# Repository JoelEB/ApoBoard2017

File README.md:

2017 Propagand-Eye
=======================================

This is the development repo for the 2017 Apogaea soldering Workshop project, the Propagand-Eye. 

For all final files for tutorials on how to hack your eyeball, please visit [https://github.com/apoboard](https://github.com/apoboard). 

To donate to this project, please send donations to joeleb on Venmo. 

This board uses an Atmega328p microcontroller (the same device in the Arduino Uno) and can be programmed with an FTDI serial adapter and the Arduino IDE. There is a DC/DC boost-converter (the PAM2401) to provide 5 volts from a single AA battery. On board are 10 addressable WS2812 LEDs (the same LEDs used on all Neopixel products). There is also an infrared (IR) transmitter/receiver pair that allows the boards to communicate with one another. A tactile button is also provided to switch through modes.

License Information
-------------------

All of these files are developed for free, for Apogaea, and for fun. It is publicly available under the GNU General Public License version 2 (the "GPL License"). For more information, please see: http://www.gnu.org/licenses/gpl-2.0.html

Copyright (c) John English, Joel Bartlett, 2017 Licensing: GPL v2

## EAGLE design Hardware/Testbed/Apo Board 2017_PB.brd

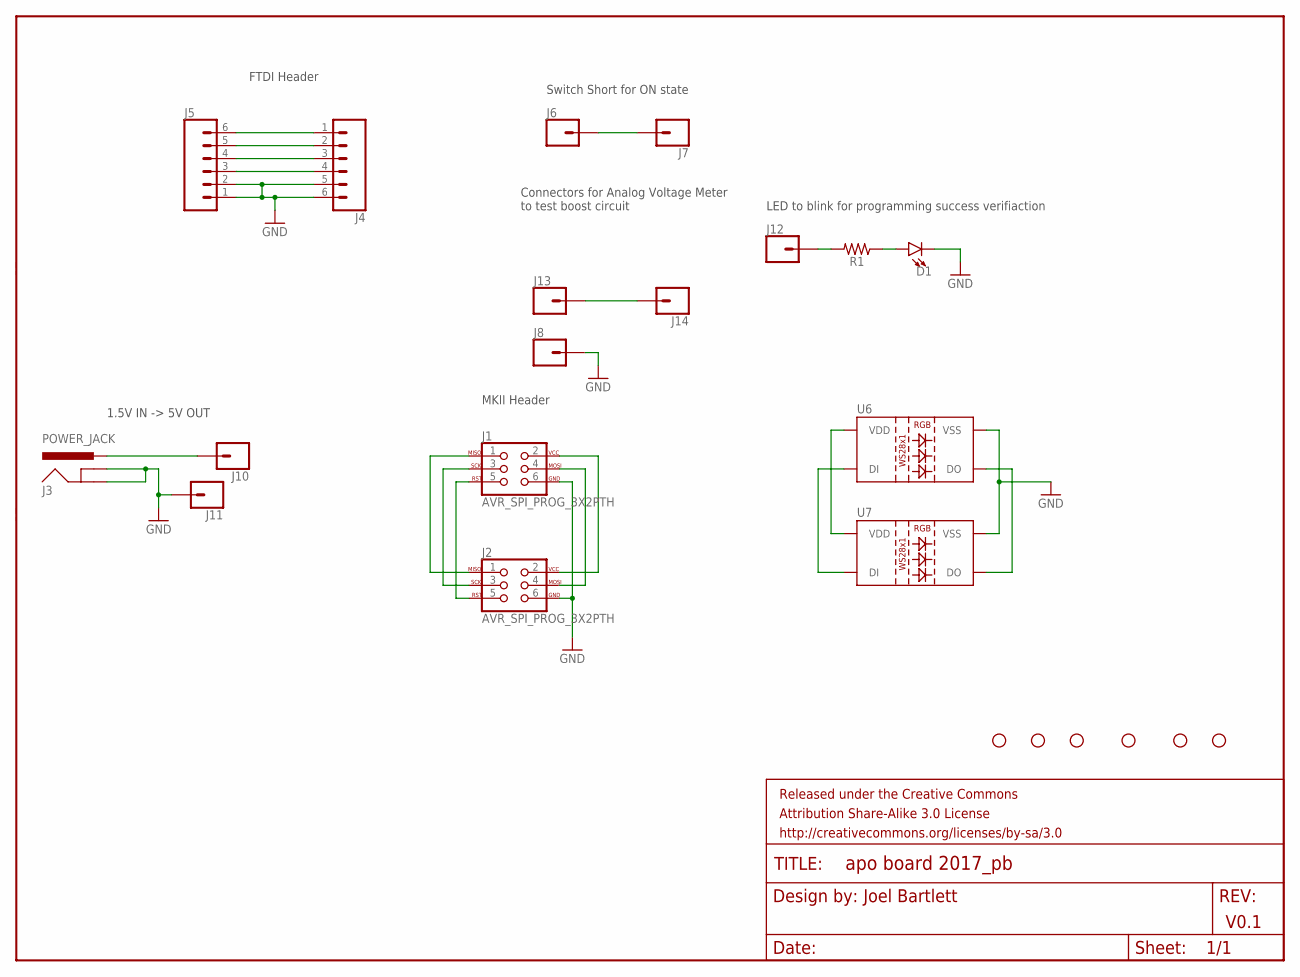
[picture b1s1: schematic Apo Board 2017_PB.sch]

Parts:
D1: LED5MM; LED_5MM
FRAME1: FRAME-LETTER; CREATIVE_COMMONS
H1, H2, H3, H4, H5, H6: STAND-OFF
J1, J2: AVR_SPI_PROG_3X2PTH; 2X3
J3: POWER_JACK; POWER_JACK_PTH
J4, J5: CONN_06LONGPADS; 1X06_LONGPADS
J6, J7, J8, J10, J11, J12, J13, J14: CONN_01PTH_LONGPAD; 1X01_LONGPAD
R1: AXIAL-0.3-KIT
U6, U7: LED-TRICOLOR-5050-ICWS2812-THRU-KIT; LED-RGB-THRU-KIT

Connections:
GND: D1.K (C), J1.6, J2.6, J3.GND, J3.GNDBREAK, J4.5, J4.6, J5.1, J5.2, J8.1, J11.1, U6.3 (VSS), U7.3 (VSS)
unnamed: J3.PWR, J10.1
unnamed: J1.4, J2.4
unnamed: J1.2, J2.2
unnamed: J1.5, J2.5
unnamed: J1.3, J2.3
unnamed: J1.1, J2.1
unnamed: U6.4 (DO), U7.4 (DO)
unnamed: J4.4, J5.3
unnamed: J4.3, J5.4
unnamed: J4.2, J5.5
unnamed: J4.1, J5.6
unnamed: J6.1, J7.1
unnamed: D1.A, R1.P$1 (1)
unnamed: J12.1, R1.P$2 (2)
unnamed: U6.1 (DI), U7.1 (DI)
unnamed: J13.1, J14.1
unnamed: U6.2 (VDD), U7.2 (VDD)

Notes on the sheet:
Joel Bartlett
V0.1
Switch Short for ON state
FTDI Header
1.5V IN -> 5V OUT
MKII Header
Connectors for Analog Voltage Meter to test boost circuit
LED to blink for programming success verifiaction

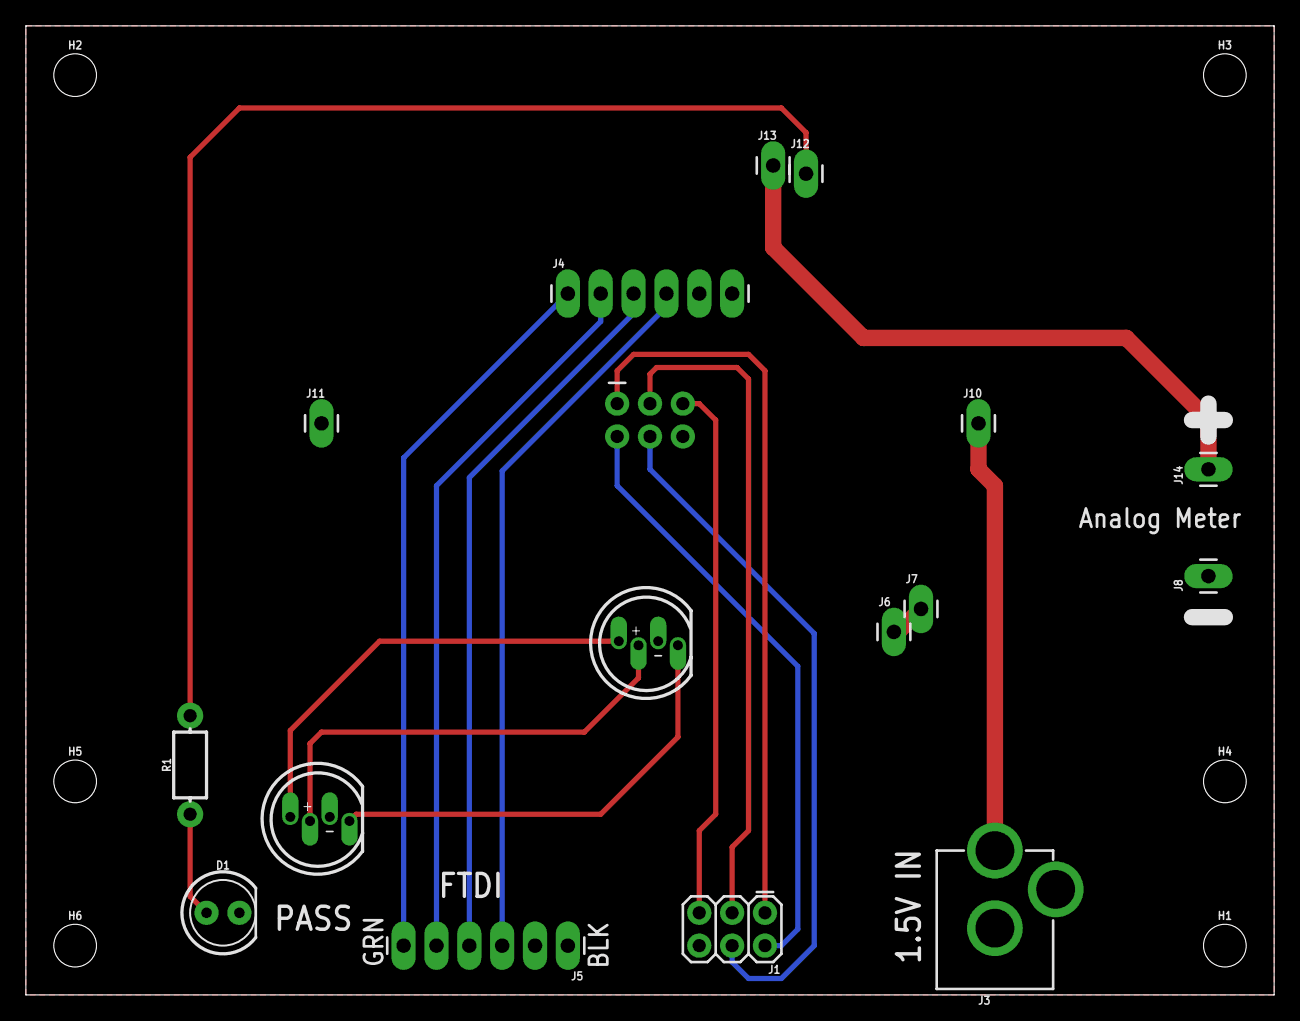
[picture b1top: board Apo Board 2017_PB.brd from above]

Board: 2 copper layers, 96.5 x 74.9 mm, 24 parts (1 on the bottom side), 18 nets.

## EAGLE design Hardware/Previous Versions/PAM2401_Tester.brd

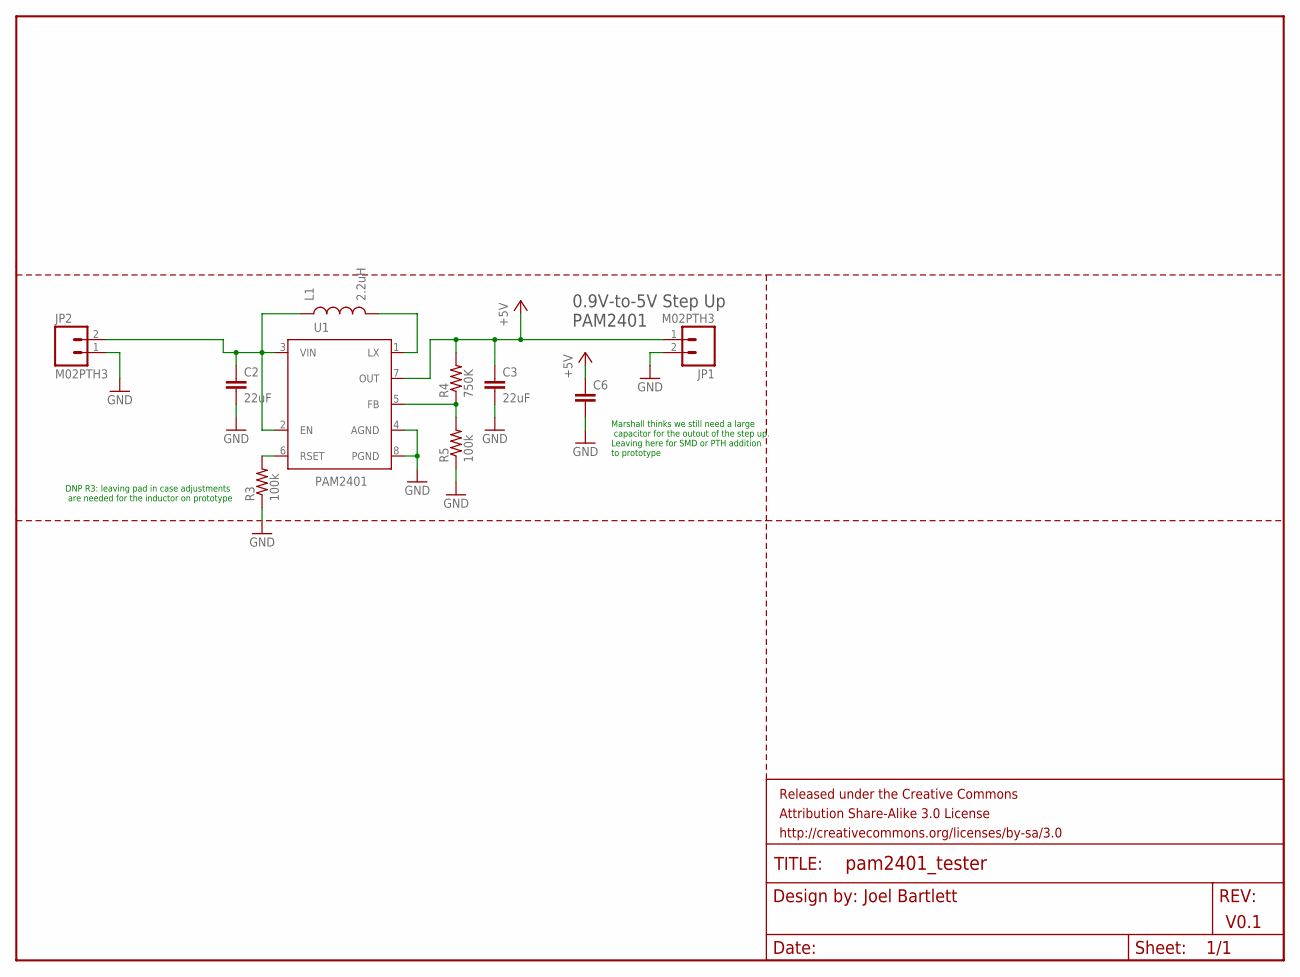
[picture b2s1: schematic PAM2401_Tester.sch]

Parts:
C2, C3: 22uF; 0805
C6: CAP1206; 1206
FRAME1: FRAME-LETTER; CREATIVE_COMMONS
JP1, JP2: M02PTH3; 1X02_LONGPADS
L1: 2.2uH; CR54
R3, R5: 100k; 0603-RES
R4: 750K; 0603-RES
U1: PAM2401; MSOP8

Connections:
+5V: C3.1, C6.1, JP1.1, R4.2, U1.7 (OUT)
+BATT_RAW: C2.1, JP2.2, L1.P$1 (1), U1.2 (EN), U1.3 (VIN)
GND: C2.2, C3.2, C6.2, JP1.2, JP2.1, R3.1, R5.1, U1.4 (AGND), U1.8 (PGND)
unnamed: R3.2, U1.6 (RSET)
unnamed: L1.P$2 (2), U1.1 (LX)
unnamed: R4.1, R5.2, U1.5 (FB)

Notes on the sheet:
Joel Bartlett
0.9V-to-5V Step Up PAM2401
DNP R3: leaving pad in case adjustments are needed for the inductor on prototype
Marshall thinks we still need a large capacitor for the outout of the step up. Leaving here for SMD or PTH addition to prototype
V0.1

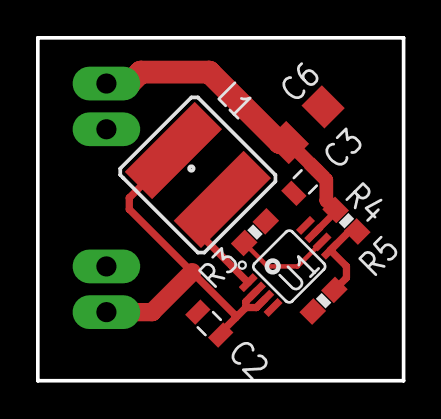
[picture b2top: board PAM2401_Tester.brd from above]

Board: 2 copper layers, 20.3 x 19.1 mm, 11 parts (0 on the bottom side), 6 nets.

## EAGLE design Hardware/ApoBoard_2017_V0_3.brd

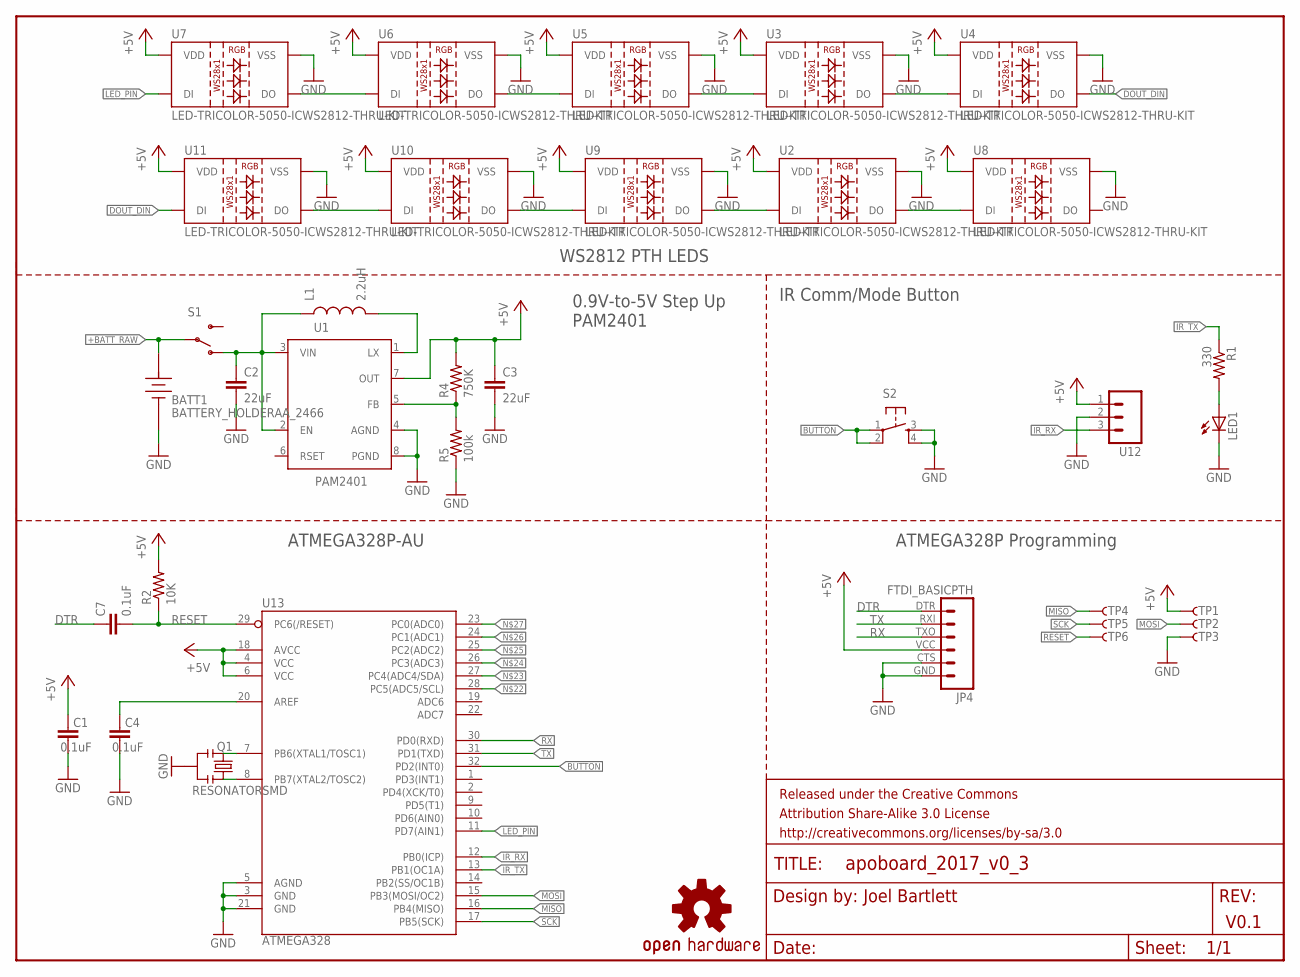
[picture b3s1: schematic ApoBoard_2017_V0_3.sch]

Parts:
BATT1: BATTERY_HOLDERAA_2466; BATT_HOLDER_AA_2466
C1, C4, C7: 0.1uF; 0402-CAP
C2, C3: 22uF; 0805
FRAME1: FRAME-LETTER; CREATIVE_COMMONS
JP4: FTDI_BASICPTH; FTDI_BASIC
L1: 2.2uH; CDRH2D09
LED1: LED5MM-KIT
LOGO1: OSHW-LOGOS; OSHW-LOGO-S
Q1: RESONATORSMD; RESONATOR-SMD
R1: 330; AXIAL-0.3-KIT
R2: 10K; 0402-RES
R4: 750K; 0603-RES
R5: 100k; 0603-RES
S1: SWITCH-SPSTKIT; SWITCH-SPDT_KIT
S2: TAC_SWITCHPTH; TACTILE-PTH
TP1, TP2, TP3, TP4, TP5, TP6: TP-3x5; PAD.03X.05
U1: PAM2401; MSOP8
U2, U3, U4, U5, U6, U7, U8, U9, U10, U11: LED-TRICOLOR-5050-ICWS2812-THRU-KIT; LED-RGB-THRU-KIT
U12: M03IR_RECEIVER; 1X03_IR_RECEIVER
U13: ATMEGA328; TQFP32-08

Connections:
+5V: C1.2, C3.1, JP4.VCC (4), R2.2, R4.2, TP1.P$1, U1.7 (OUT), U2.2 (VDD), U3.2 (VDD), U4.2 (VDD), U5.2 (VDD), U6.2 (VDD), U7.2 (VDD), U8.2 (VDD), U9.2 (VDD), U10.2 (VDD), U11.2 (VDD), U12.1, U13.4 (VCC), U13.6 (VCC), U13.18 (AVCC)
+BATT_RAW: BATT1.P, S1.2
AREF: C4.2, U13.20 (AREF)
BUTTON: S2.1, S2.2, U13.32 (PD2(INT0))
DOUT_DIN: U4.4 (DO), U11.1 (DI)
DTR: C7.1, JP4.DTR (1)
GND: BATT1.N, C1.1, C2.2, C3.2, C4.1, JP4.CTS (5), JP4.GND (6), LED1.K (C), Q1.2, R5.1, S2.3, S2.4, TP3.P$1, U1.4 (AGND), U1.8 (PGND), U2.3 (VSS), U3.3 (VSS), U4.3 (VSS), U5.3 (VSS), U6.3 (VSS), U7.3 (VSS), U8.3 (VSS), U9.3 (VSS), U10.3 (VSS), U11.3 (VSS), U12.2, U13.3 (GND), U13.5 (AGND), U13.21 (GND)
IR_RX: U12.3, U13.12 (PB0(ICP))
IR_TX: R1.P$1 (1), U13.13 (PB1(OC1A))
LED_PIN: U7.1 (DI), U13.11 (PD7(AIN1))
MISO: TP4.P$1, U13.16 (PB4(MISO))
MOSI: TP2.P$1, U13.15 (PB3(MOSI/OC2))
unnamed: U6.1 (DI), U7.4 (DO)
unnamed: U5.1 (DI), U6.4 (DO)
unnamed: LED1.A, R1.P$2 (2)
unnamed: U3.1 (DI), U5.4 (DO)
unnamed: U3.4 (DO), U4.1 (DI)
unnamed: L1.P$2 (2), U1.1 (LX)
unnamed: U10.1 (DI), U11.4 (DO)
unnamed: C2.1, L1.P$1 (1), S1.1 (O), U1.2 (EN), U1.3 (VIN)
unnamed: U9.1 (DI), U10.4 (DO)
unnamed: R4.1, R5.2, U1.5 (FB)
unnamed: U2.1 (DI), U9.4 (DO)
unnamed: U2.4 (DO), U8.1 (DI)
unnamed: Q1.1, U13.8 (PB7(XTAL2/TOSC2))
unnamed: Q1.3, U13.7 (PB6(XTAL1/TOSC1))
RESET: C7.2, R2.1, TP6.P$1, U13.29 (PC6(/RESET))
RX: JP4.TXO (3), U13.30 (PD0(RXD))
SCK: TP5.P$1, U13.17 (PB5(SCK))
TX: JP4.RXI (2), U13.31 (PD1(TXD))

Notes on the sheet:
Joel Bartlett
WS2812 PTH LEDS
0.9V-to-5V Step Up PAM2401
IR Comm/Mode Button
ATMEGA328P-AU
ATMEGA328P Programming
V0.1

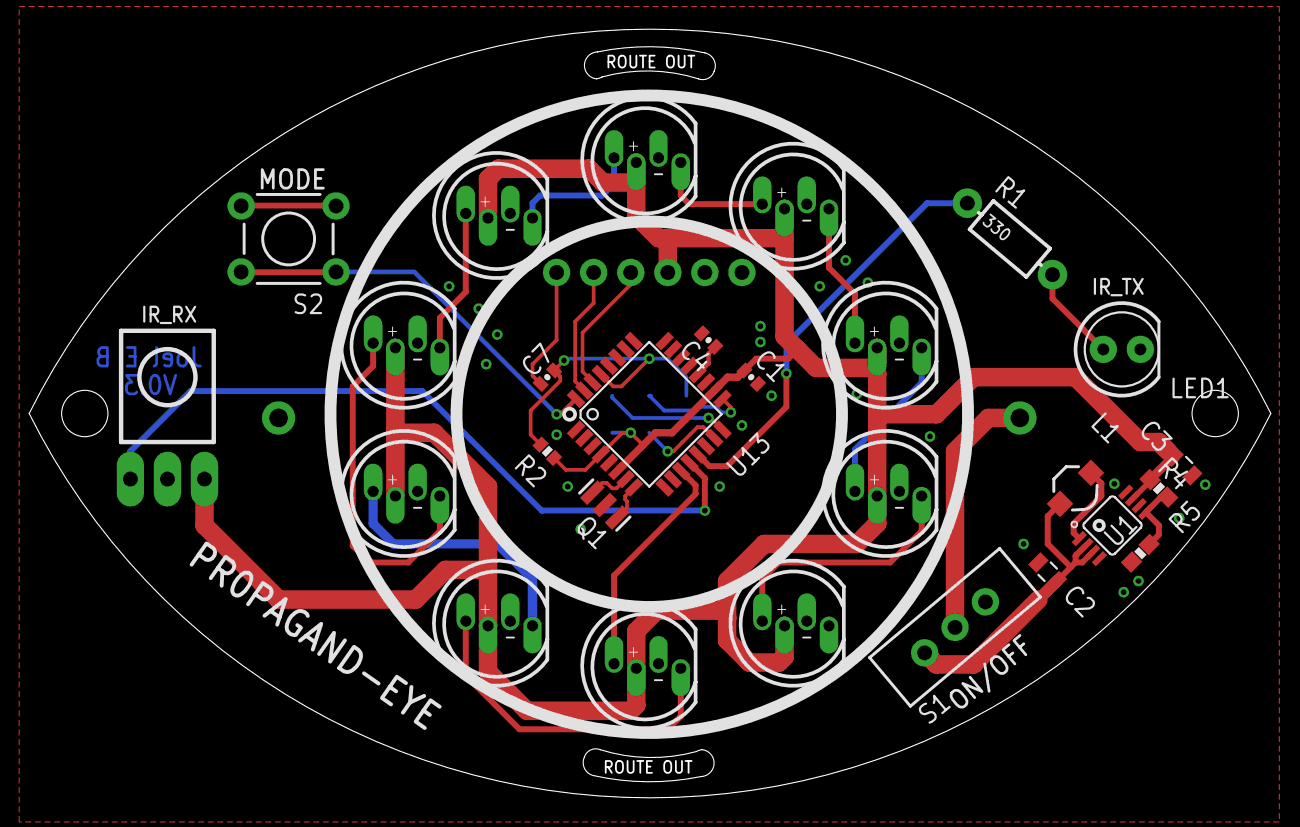
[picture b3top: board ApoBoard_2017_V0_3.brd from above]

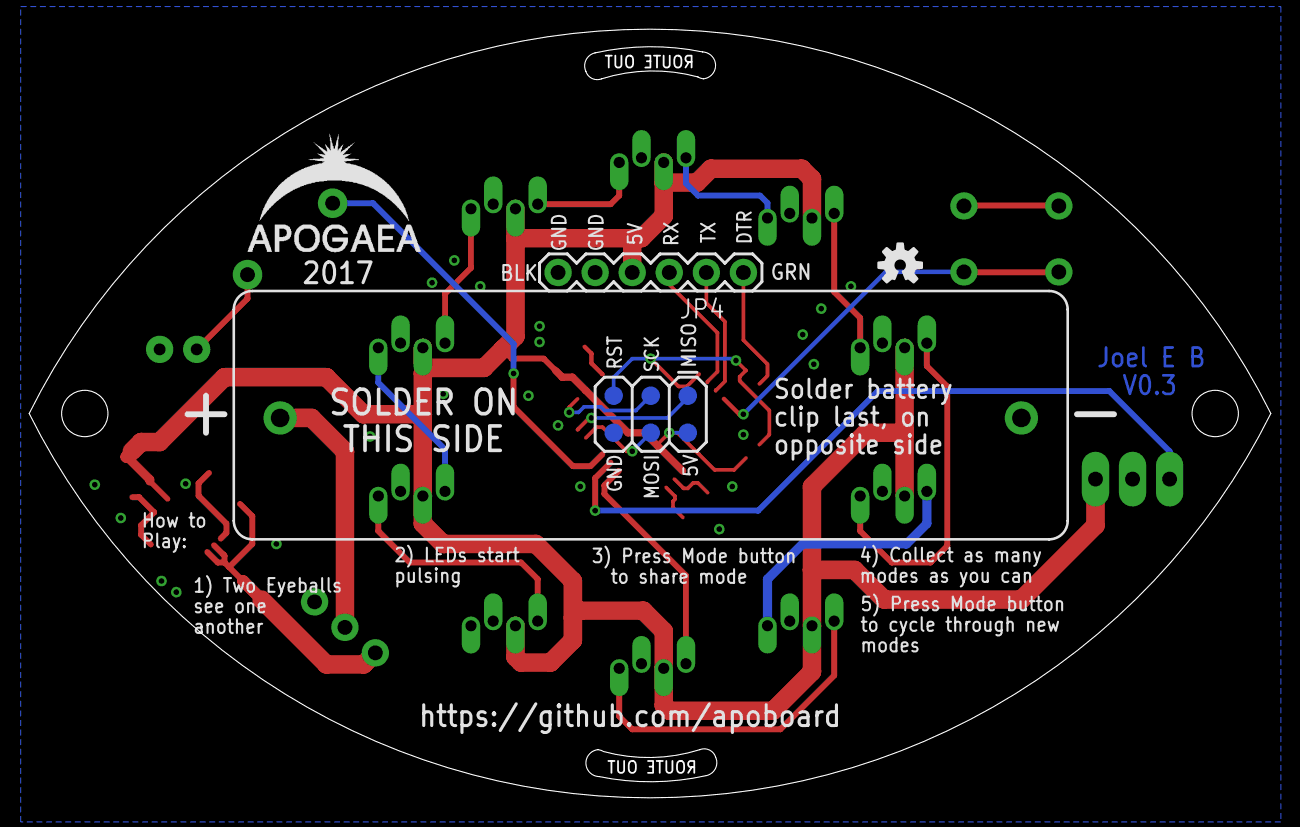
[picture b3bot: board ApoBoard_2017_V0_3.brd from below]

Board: 2 copper layers, 85.1 x 52.7 mm, 38 parts (10 on the bottom side), 30 nets.

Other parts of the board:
U$2: APOLOGO

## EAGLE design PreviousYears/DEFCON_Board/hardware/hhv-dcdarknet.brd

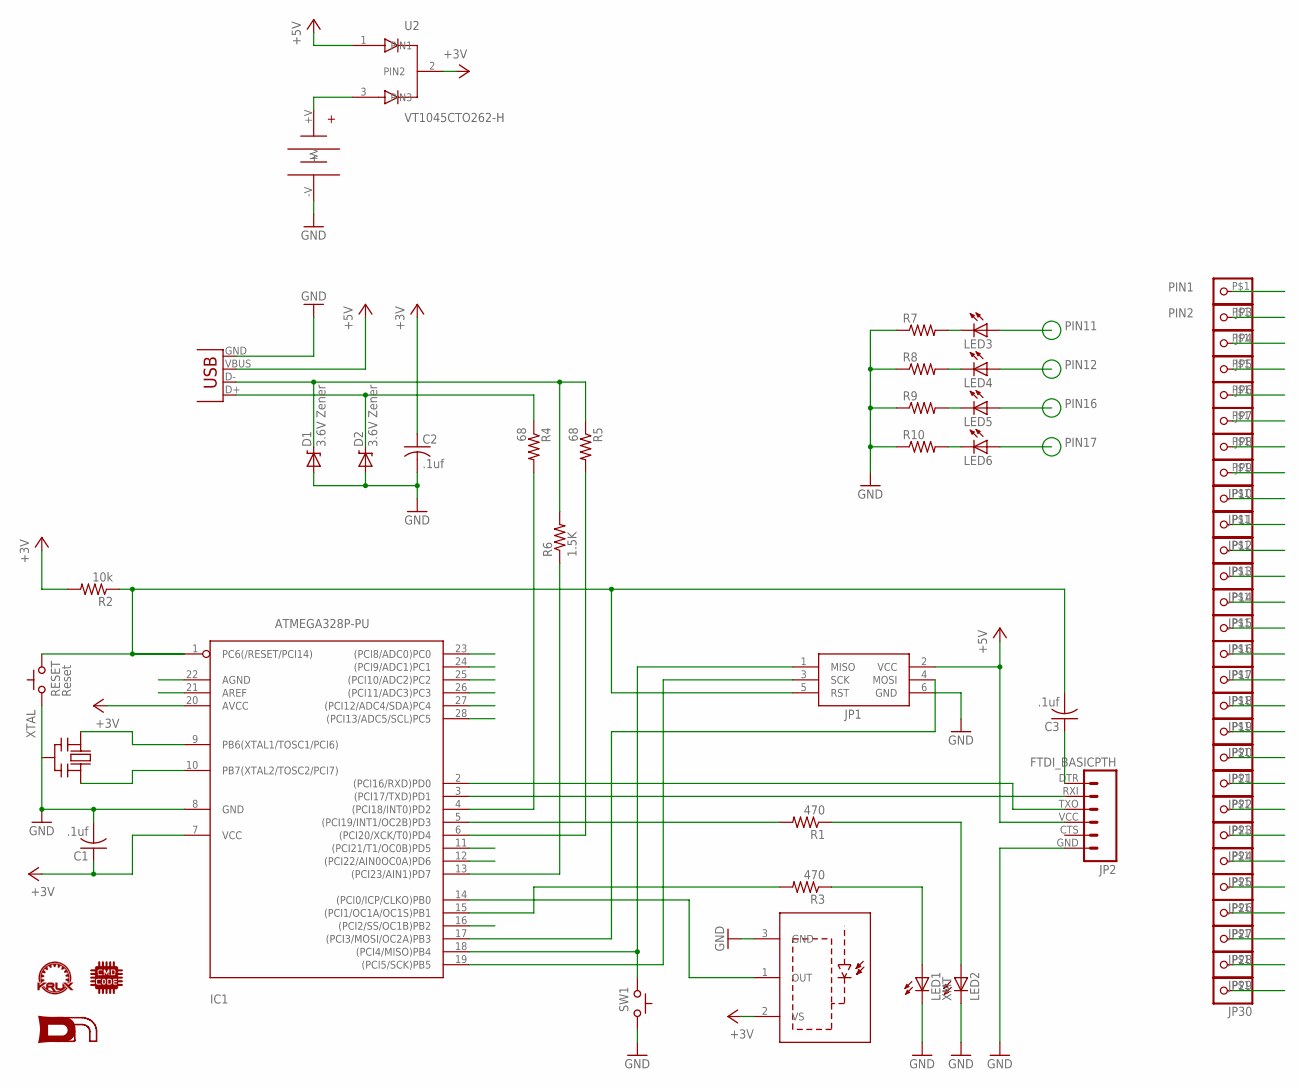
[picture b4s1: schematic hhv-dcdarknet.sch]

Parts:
C1, C2, C3: .1uf; C025-030X050
D1, D2: 3.6V Zener; DIODE-ZENER
IC1: ATMEGA328P-PU; DIL28-3
JP1: JP1; AVRISP
JP2: FTDI_BASICPTH; FTDI_BASIC
JP3, JP4, JP5, JP6, JP7, JP8, JP9, JP10, JP11, JP12, JP13, JP14, JP15, JP16, JP17, JP18, JP19, JP20, JP21, JP22, JP23, JP26, JP28: PINHD-1X11X1_SQUARE; 1X1-SMALL_CUT
JP24, JP25, JP27, JP29, JP30: PINHD-1X11X1-SMALL; 1X1-SMALL
LED1: XMT; LED5MM-FLAT
LED2: LED5MM-FLAT
LED3, LED4, LED5, LED6: LED1206; LED-1206
R1, R3: 470; AXIAL-0.3
R2: 10k; AXIAL-0.3
R4, R5: 68; AXIAL-0.3
R6: 1.5K; AXIAL-0.3
R7, R8, R9, R10: RESISTOR1206; 1206
RESET: Reset; TACTILE-2PIN
SW1: SWITCH_TACTILETACTILE-2PIN; TACTILE-2PIN
U1: RCV; IR-MODULE
U2: VT1045CTO262-H; TO262-H
U$1: DN_LOGO
U$2: CMDC0DE_LOGO; CMDC0DE
U$3: KRUX_LOGO
U$5: 12BH423-GR3-CELL_NOBORDER; 3-AAA-CELL_NOBORDER
X2: USB; USB-B-PTH
XTAL: CERMOSCILL-THM; CERM_OSC

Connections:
+3V3: C1.1, C2.1, IC1.7 (VCC), IC1.20 (AVCC), JP9.P$1, JP22.P$1, R2.P$2 (2), U1.2 (VS), U2.2 (PIN2)
+5V: JP1.2 (VCC), JP2.VCC (4), U2.1 (PIN1), X2.VBUS
GND: C1.2, C2.2, D1.P$2 (A), D2.P$2 (A), IC1.8 (GND), JP1.6 (GND), JP2.GND (6), JP10.P$1, LED1.K (C), LED2.K (C), R7.1, R8.1, R9.1, R10.1, RESET.P$2 (C), SW1.P$1 (A), U1.3 (GND), U$5.-V, X2.GND, XTAL.P$2 (GND)
unnamed: C3.1, JP2.DTR (1)
unnamed: LED3.C, R7.2
unnamed: LED4.C, R8.2
unnamed: LED5.C, R9.2
unnamed: LED6.C, R10.2
unnamed: LED1.A, R3.P$1 (1)
unnamed: LED2.A, R1.P$1 (1)
unnamed: D2.P$1 (C), R4.P$1 (1), X2.D+
unnamed: U2.3 (PIN3), U$5.+V
PIN1: C3.2, IC1.1 (PC6(/RESET/PCI14)), JP1.5 (RST), JP3.P$1, R2.P$1 (1), RESET.P$1 (A)
PIN2: IC1.2 ((PCI16/RXD)PD0), JP2.TXO (3), JP4.P$1
PIN3: IC1.3 ((PCI17/TXD)PD1), JP2.RXI (2), JP5.P$1
PIN4: IC1.4 ((PCI18/INT0)PD2), JP6.P$1, R4.P$2 (2)
PIN5: IC1.5 ((PCI19/INT1/OC2B)PD3), JP7.P$1, R1.P$2 (2)
PIN6: IC1.6 ((PCI20/XCK/T0)PD4), JP8.P$1, R5.P$2 (2)
PIN9: IC1.9 (PB6(XTAL1/TOSC1/PCI6)), JP11.P$1, XTAL.P$1 (IN)
PIN10: IC1.10 (PB7(XTAL2/TOSC2/PCI7)), JP12.P$1, XTAL.P$3 (OUT)
PIN11: IC1.11 ((PCI21/T1/OC0B)PD5), JP13.P$1, LED3.A
PIN12: IC1.12 ((PCI22/AIN0OC0A)PD6), JP14.P$1, LED4.A
PIN13: IC1.13 ((PCI23/AIN1)PD7), JP15.P$1, R6.P$1 (1)
PIN14: IC1.14 ((PCI0/ICP/CLKO)PB0), JP16.P$1, U1.1 (OUT)
PIN15: IC1.15 ((PCI1/OC1A/OC1S)PB1), JP17.P$1, R3.P$2 (2)
PIN16: IC1.16 ((PCI2/SS/OC1B)PB2), JP18.P$1, LED5.A
PIN17: IC1.17 ((PCI3/MOSI/OC2A)PB3), JP1.4 (MOSI), JP19.P$1, LED6.A
PIN18: IC1.18 ((PCI4/MISO)PB4), JP1.1 (MISO), JP20.P$1, SW1.P$2 (C)
PIN19: IC1.19 ((PCI5/SCK)PB5), JP1.3 (SCK), JP21.P$1
PIN21: IC1.21 (AREF), JP23.P$1
PIN22: IC1.22 (AGND), JP24.P$1
PIN23: IC1.23 ((PCI8/ADC0)PC0), JP25.P$1
PIN24: IC1.24 ((PCI9/ADC1)PC1), JP26.P$1
PIN25: IC1.25 ((PCI10/ADC2)PC2), JP27.P$1
PIN26: IC1.26 ((PCI11/ADC3)PC3), JP28.P$1
PIN27: IC1.27 ((PCI12/ADC4/SDA)PC4), JP29.P$1
PIN28: IC1.28 ((PCI13/ADC5/SCL)PC5), JP30.P$1
USB: D1.P$1 (C), R5.P$1 (1), R6.P$2 (2), X2.D-

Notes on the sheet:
PIN11
PIN12
PIN16
PIN17

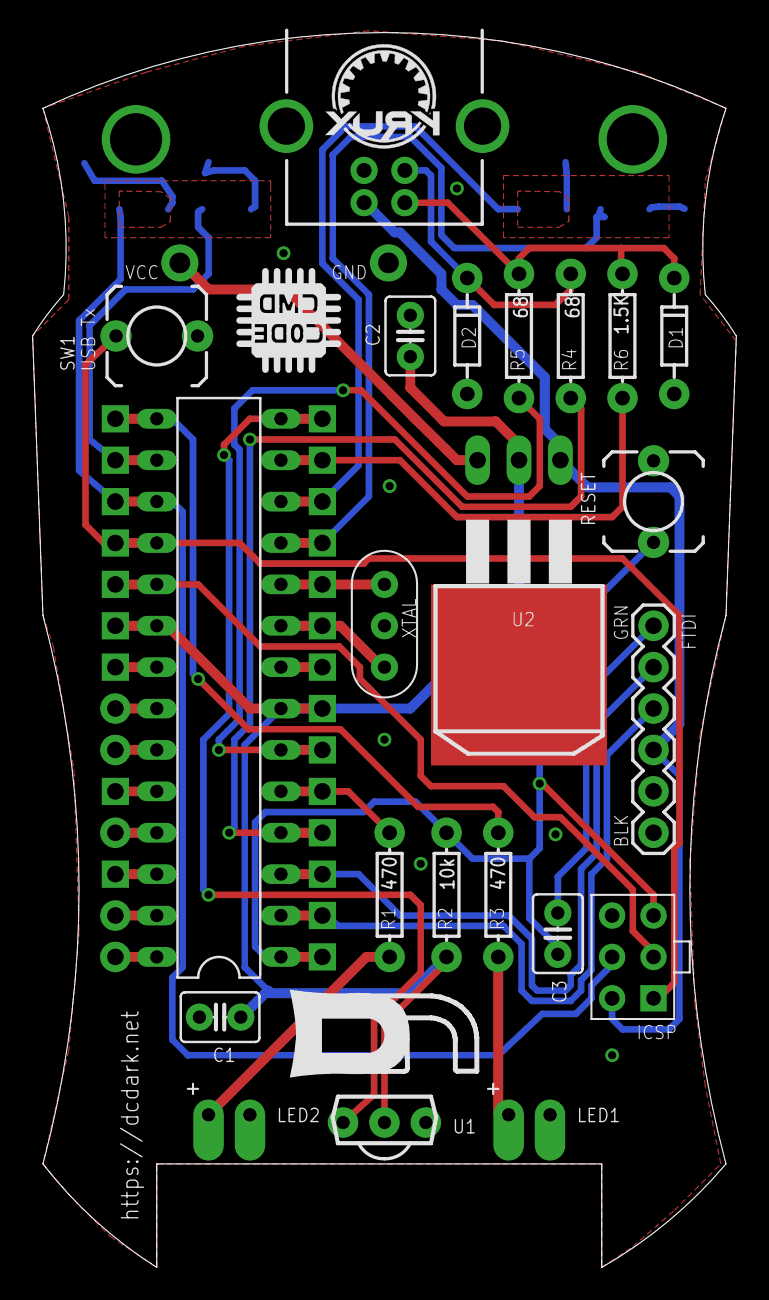
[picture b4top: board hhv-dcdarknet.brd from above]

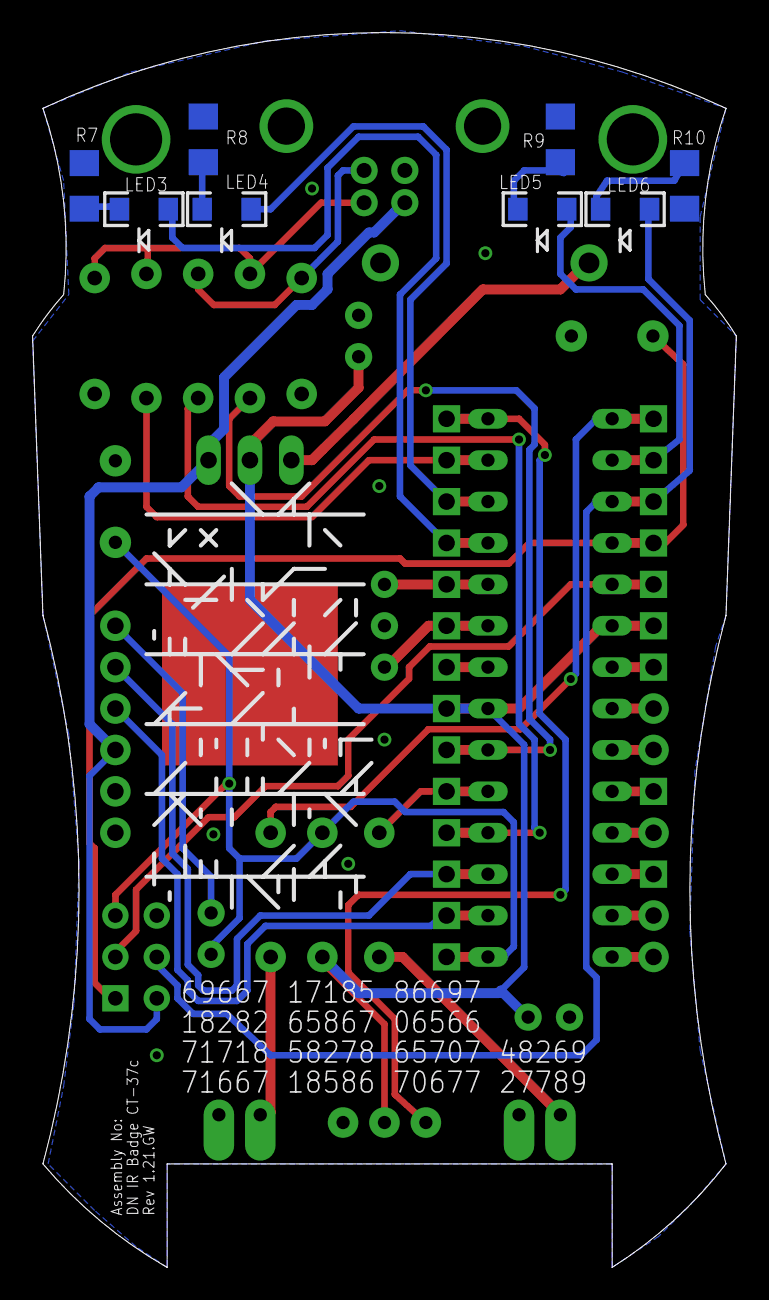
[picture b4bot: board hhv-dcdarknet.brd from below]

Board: 2 copper layers, 43.2 x 75.8 mm, 62 parts (10 on the bottom side), 38 nets.

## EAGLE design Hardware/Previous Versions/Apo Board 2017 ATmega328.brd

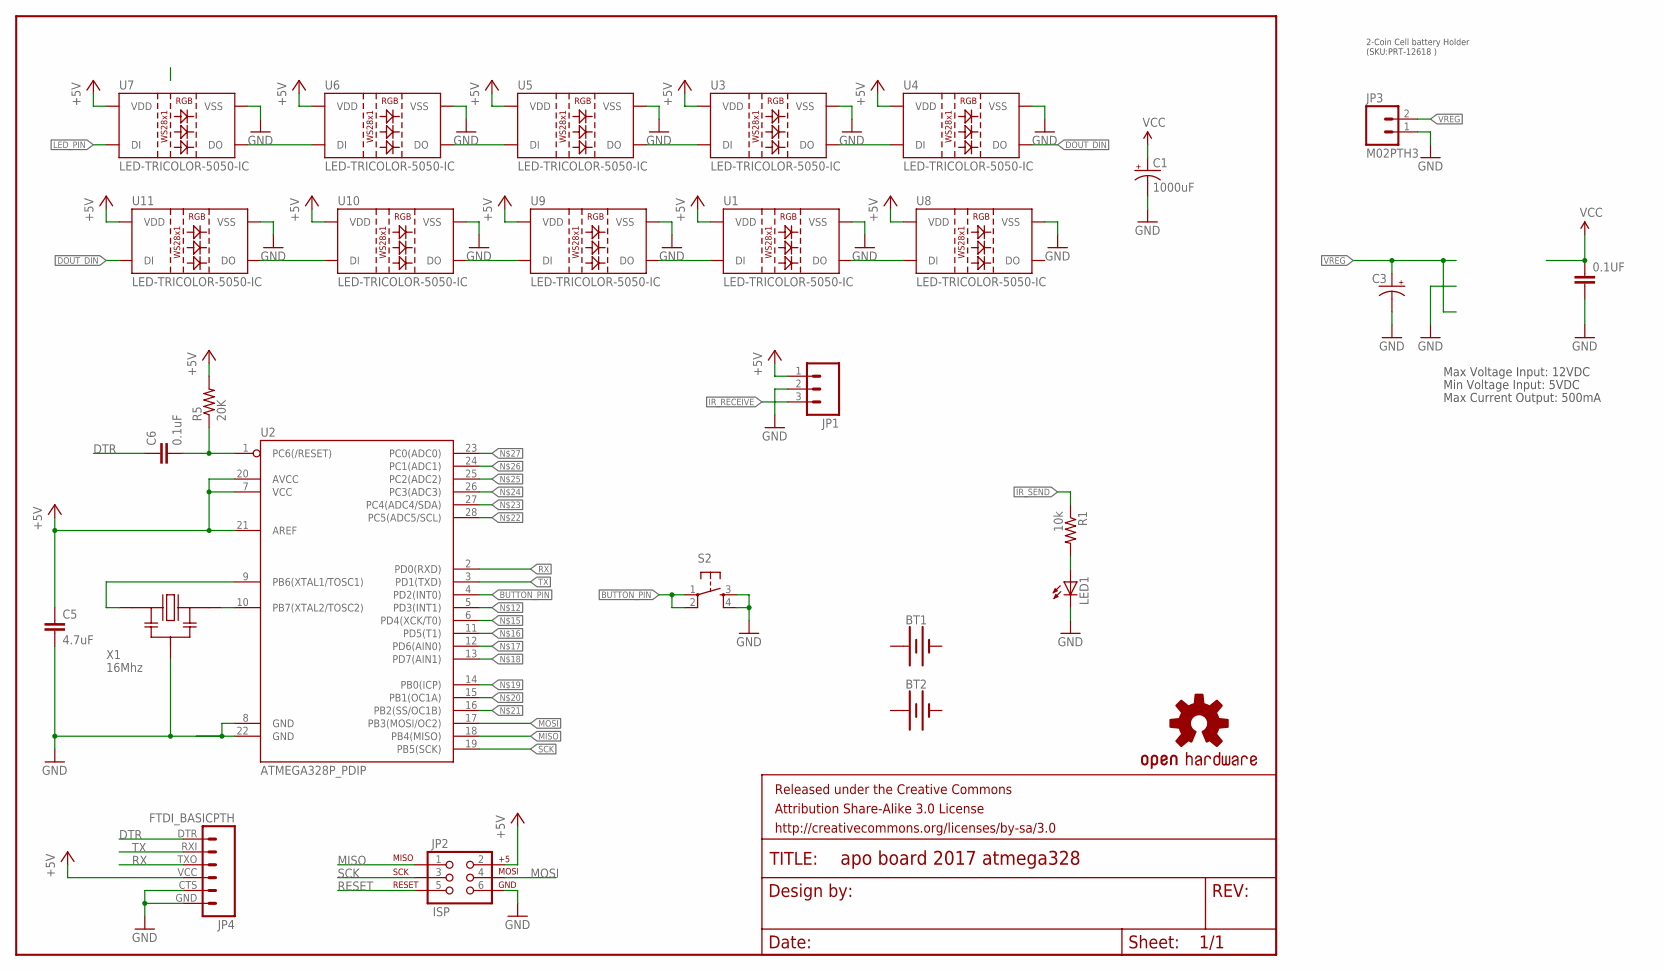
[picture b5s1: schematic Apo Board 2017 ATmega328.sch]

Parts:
0.1UF: CAPKIT; CAP-PTH-SMALL-KIT
BT1, BT2: BATTERY-AAA
C1: 1000uF; CPOL-RADIAL-10UF-25V
C3: CAP_POLPTH2; CPOL-RADIAL-10UF-25V
C5: 4.7uF; CAP-PTH-SMALL-KIT
C6: 0.1uF; CAP-PTH-SMALL-KIT
FRAME1: FRAME-LETTER; CREATIVE_COMMONS
JP1: M03PTH; 1X03
JP2: ISP; 2X3
JP3: M02PTH3; 1X02_LONGPADS
JP4: FTDI_BASICPTH; FTDI_BASIC
LED1: LED5MM
LOGO1: OSHW-LOGOS; OSHW-LOGO-S
R1: 10k; AXIAL-0.4
R5: 20K; AXIAL-0.3-KIT
S2: TAC_SWITCHPTH; TACTILE-PTH
U1, U3, U4, U5, U6, U7, U8, U9, U10, U11: LED-TRICOLOR-5050-IC; LED-RGB-THRU
U2: ATMEGA328P_PDIP; DIL28-3
X1: 16Mhz; CERAMIC_RESONATOR_ZTT

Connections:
+: BT1.PWR@1 (+), BT2.PWR@1 (+)
+5V: C5.1, JP1.1, JP2.2, JP4.VCC (4), R5.P$2 (2), U1.2 (VDD), U2.7 (VCC), U2.20 (AVCC), U2.21 (AREF), U3.2 (VDD), U4.2 (VDD), U5.2 (VDD), U6.2 (VDD), U7.2 (VDD), U8.2 (VDD), U9.2 (VDD), U10.2 (VDD), U11.2 (VDD)
-: BT1.GND@1 (-), BT2.GND@1 (-)
BUTTON_PIN: S2.1, S2.2, U2.4 (PD2(INT0))
DOUT_DIN: U4.4 (DO), U11.1 (DI)
DTR: C6.1, JP4.DTR (1)
GND: 0.1UF.2, C1.2 (-), C3.2 (-), C5.2, JP1.2, JP2.6, JP3.1, JP4.CTS (5), JP4.GND (6), LED1.K (C), S2.3, S2.4, U1.3 (VSS), U2.8 (GND), U2.22 (GND), U3.3 (VSS), U4.3 (VSS), U5.3 (VSS), U6.3 (VSS), U7.3 (VSS), U8.3 (VSS), U9.3 (VSS), U10.3 (VSS), U11.3 (VSS), X1.P$2
IR_RECEIVE: JP1.3
IR_SEND: R1.P$1 (1)
LED_PIN: U7.1 (DI)
MISO: JP2.1, U2.18 (PB4(MISO))
MOSI: JP2.4, U2.17 (PB3(MOSI/OC2))
unnamed: U6.1 (DI), U7.4 (DO)
unnamed: U5.1 (DI), U6.4 (DO)
unnamed: LED1.A, R1.P$2 (2)
unnamed: U2.9 (PB6(XTAL1/TOSC1)), X1.P$1
unnamed: U3.1 (DI), U5.4 (DO)
unnamed: U3.4 (DO), U4.1 (DI)
unnamed: U2.10 (PB7(XTAL2/TOSC2)), X1.P$3
unnamed: U10.1 (DI), U11.4 (DO)
unnamed: C6.2, R5.P$1 (1), U2.1 (PC6(/RESET))
unnamed: U9.1 (DI), U10.4 (DO)
unnamed: U1.1 (DI), U9.4 (DO)
unnamed: U1.4 (DO), U8.1 (DI)
RESET: JP2.5
RX: JP4.TXO (3), U2.2 (PD0(RXD))
SCK: JP2.3, U2.19 (PB5(SCK))
TX: JP4.RXI (2), U2.3 (PD1(TXD))
VCC: 0.1UF.1, C1.1 (+)
VREG: C3.1 (+), JP3.2

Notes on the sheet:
2-Coin Cell battery Holder (SKU:PRT-12618 )
Max Voltage Input: 12VDC
Max Current Output: 500mA
Min Voltage Input: 5VDC

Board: 2 copper layers, 29 parts (1 on the bottom side), 26 nets, no tracks yet.

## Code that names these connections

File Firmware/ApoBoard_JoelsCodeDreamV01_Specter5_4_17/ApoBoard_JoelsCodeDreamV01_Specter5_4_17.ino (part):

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#define NeoPIN 7// was 10
#define NeoLEDs 10 //was 10 //number of addressable LEDs
#define NumEffects 10
#define BUTTON_PIN 2
#define debounce_time 10 // button debounce in ms
// IR Parameters
#define IR_RX 8 //was 8
#define IR_TX 9 //was 9
#define IR_BAUD 300
IRSerial irSerial(IR_RX, IR_TX, false, true);

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
/////////// GLOBALS /////////////////
bool button_shadow = false;
int button = BUTTON_PIN;
int photopot = A1;
int colorModeMax = 5;
int colorMode = 0;
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
    void updateButton() {
     if (bounceState == WATCH_BUTTON) {
        boolean currentButtonState = digitalRead(BUTTON_PIN);
        if (previousButtonState != currentButtonState) {
          bounceState = IGNORE_BUTTON;
          previousMicros = micros();
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      if (bounceState == IGNORE_BUTTON) {
        unsigned long currentMicros = micros();
        if ((unsigned long)(currentMicros - previousMicros) >= buttonWaitInterval) {
          debouncedButtonState = digitalRead(BUTTON_PIN);
          bounceState = WATCH_BUTTON;
        }
      }
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Adafruit_NeoPixel strip = Adafruit_NeoPixel(NeoLEDs, NeoPIN, NEO_GRB + NEO_KHZ800);

// Main morse LED
#define LED_PIN 3



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  uint32_t returnTime = millis() + pauseFor;

  while (millis() < returnTime) {
    /*if (digitalRead(BUTTON_PIN) == LOW) {
      long buttonStart = millis();
      while(digitalRead(BUTTON_PIN) == LOW && false) {
        if (millis() - buttonStart > 2000) {
          buttonStart = 0;  // Flag to not dump USB
          break;
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  irSerial.begin(IR_BAUD);
  irSerial.listen();
  digitalWrite(IR_TX, LOW); // For some reason, the TX line starts high and wastes some battery.
  pinMode(IR_RX, INPUT_PULLUP);
  pinMode(BUTTON_PIN, INPUT_PULLUP);
  delay(200);  // Reset "debounce"

  // Swetup the IR buffers and timers.
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
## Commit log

2017-03-16 ATMega328 Version
2017-03-28 Adding ATmega328 versions
2017-03-29 Cleanup
2017-03-31 Power Tests
2017-04-04 Added layout with PAM2401, cleanup folders
2017-04-06 Added Deacon board files. finished prelim layout
2017-04-07 Final touches before review
2017-04-07 Fixing Natural Jumper and few moonier text tweaks
2017-04-08 increased +5v trace width, moved all power traces to top layer, added a fair amount of sitching vias
2017-04-08 Adding testbed
2017-04-10 Final version for Prototypes V0.1 and GERBERS
2017-04-10 Final version ordered for photos V0.1
2017-04-11 V0.2 Prototype and GERBERS
    Added Kit footprints, updated silk, charged mounting holes, Named
    board, added year,
2017-04-11 Adding PAM_Tester board
2017-04-12 Specter's code 1st drop
2017-04-12 specter adds phrase added to README.md
2017-04-12 try/foo added
2017-04-13 Cleanup and adding Spec7er's code
2017-04-13 Adding extra .zip berbers
2017-04-15 SPECTER added brightness
2017-04-18 Updating Battery footprint
2017-04-22 Updating Code to match photo PCBs
2017-04-22 Adding V0.3 PCB
2017-04-25 V1.0 Final version ordered
2017-04-29 portal effect added. also: now color tables are used for effect colors. colorsets may be accessed by passing the colorset number and colorset object to an effect. I am working on integrating better w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
2017-04-29 colorsets now. Portal animation example V2
2017-04-29 Spider animation, Spider2 animation, Portal animation example V2
2017-04-29 multi effects switch. 5 simple effects so far.
2017-05-04 Adding V2 code
    adds colorsets.h and added zigzag animation
2017-05-04 button debounce. merged code.
2017-05-05 Added Portal 2 animation, can't get button to work
2017-05-05 Revision of button debounce and merged code... did not have a setup to test with since I left it at SSD but it was working for me. IR still in process.
2017-05-05 merged & fixed & verifed button code and new effects
2017-05-06 Adding Loading Effect
2017-05-06 can we merge - if you can read this then the answer is yes we can!
2017-05-07 Adding hypnotaod animation
2017-05-07 Adding lots of color sets
    Cleaned up and added close to final color sets, Cleaned up spider
    animations, Added campmate code to put on boards for campmates after
    beta test so they have all modes and colors. Randomizing colorists as
    we increment through the animations.
2017-05-07 gene exchange + master programming mode VS 1 - some bugs still but basic function. Collect up to 20 genes. Any device can be put into PROGRAMMER mode by holding down button for 10+ seconds. In PROGRA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
2017-05-08 EEPROM working now. Stores 20 genes with CRC16. Improved stack/heap use a little. Fixed crazy flashing in PROGRAMMER mode.
2017-05-09 Memory optimizations. Getting stuff out of RAM and into FLASH where appropriate. Added pacmania effect. Kinda lame.
2017-05-10 fix v2 fuckup due to poor git management by specter restored from 1171ec4
2017-05-10 fixed bug in debounce causeing phantom keypress
2017-05-10 sorry i got so escited but its sooo fun to playwith thanks hardware desginer joel
2017-05-11 Updating Testbed - almost finished
2017-05-11 Adding Joel Colorsets to V3
    Adding my colors sets, which are close to finished if not finished.
    Also fine tuning and tweaking some of the animation timing, brightness,
    and colors.
2017-05-12 Added utilities. Now anyone with a serial connection can change eeprom values, dump eeprom, and reset eeprom. Send ? to device over serial to see the help menu
2017-05-12 Pogo Bed finished.
    Finished making pogoed programming and testing fixture. Moving to
    Hardware Folder
2017-05-13 Fixed 'learn gene' bug causing multiple genes of same type being stored. Proper gene function is confirmed on SPECTER's side. Also, button need only be pressed for less than 1second to 'learn' new ge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
2017-05-14 Effect 13 , pacman's revenge, a short film done in 10 leds.
2017-05-17 bug fixes
2017-05-17 my own effect
2017-05-17 refining bottom layer of testbed
2017-05-19 Autoprogrammer tests
2017-05-20 just a few test files for auto-programmer
2017-05-20 only test code right now
2017-05-22 Batch programs eeprom or epprom+flash. Not tested
2017-05-22 Master Gene list vs .01 With NO culling or really testing. 111 Genes total
2017-05-22 iHEX of ApoV03 + bootloader
2017-05-22 not much changed. still works.
2017-05-23 Works. Tested most functions. Clears the hfuse EEPROMsave bit.
2017-05-23 added notes about atmega328 fuses
2017-05-23 bugfixes. Also, now writes badgeNum to EEPROM
2017-05-23 now with help system. also, some important batch write bugfixes
2017-05-23 no longer includes colorset0
2017-05-23 Help system. Now reads badgeNum with cmd read_genes. Also, cleaned up terminal messages a little by removing avrdude connection OK messages
2017-05-23 put color defines at top <again>
2017-05-24 Re-adding Joel colorsets
2017-05-24 MaxEffects = 16. MaxColors = 14. No blacklist.
2017-05-24 made moar maclike doh!
2017-05-24 Adding AVR folder
2017-05-24 Removing Mac AVR folder
2017-05-27 put avrdude cmd back
2017-05-27 changes for Tuesday night at SSD
2017-05-27 hypnotoad returns as effect #15. Optimized too.
2017-05-27 some effects tweaks
2017-05-28 fixes to moar effects + more progmem
2017-05-28 Adding testbed success LED to firmware
    LED on A5 now blinks in setup() to visually verify a successful upload
    of the firmware.
2017-05-29 Effects bugfixes a. Much IR debug enabled - I will comment out later srry.
2017-05-29 Programmer post beta... perhaps permaturely...
2017-05-29 small script to copy firmware from ApoBoardV03.ino directory into Programmer directory
2017-05-29 still works
2017-05-29 remove pac eye. Fix eye blink. mostly eyes really.
2017-05-29 fixed rollover. fixed fill bug in terminal. poc for mating dance
2017-05-29 hex files as of 12:15 am
2017-05-30 Awkward sex no can happen. Better IR comm timing too. Makes a HUGE difference... HUGE.
2017-05-31 many last minute bug fixes to timing, mating=green, wrap(in,limit) and others
2017-05-31 added red,green,and blue colorsets
2017-05-31 Joel told me to make this the Final firmware push for ApoGaea. I luv you all. Have fun
2017-05-31 minor last minute bugfixes... to be honest I can't remember
2017-05-31 3 more complementary color sets
2017-05-31 final master gene list
2017-05-31 the real final test push...
2017-05-31 renamed as final
2017-06-07 A little guide for advanced users

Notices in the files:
parts and their libraries:
SparkFun-Connectors: Licensing: CC v3.0 Share-Alike You are welcome to use this library for commercial purposes.
SparkFun-Aesthetics: Released under the Creative Commons Attribution Share-Alike 3.0 License
SparkFun-Aesthetics: http://creativecommons.org/licenses/by-sa/3.0
